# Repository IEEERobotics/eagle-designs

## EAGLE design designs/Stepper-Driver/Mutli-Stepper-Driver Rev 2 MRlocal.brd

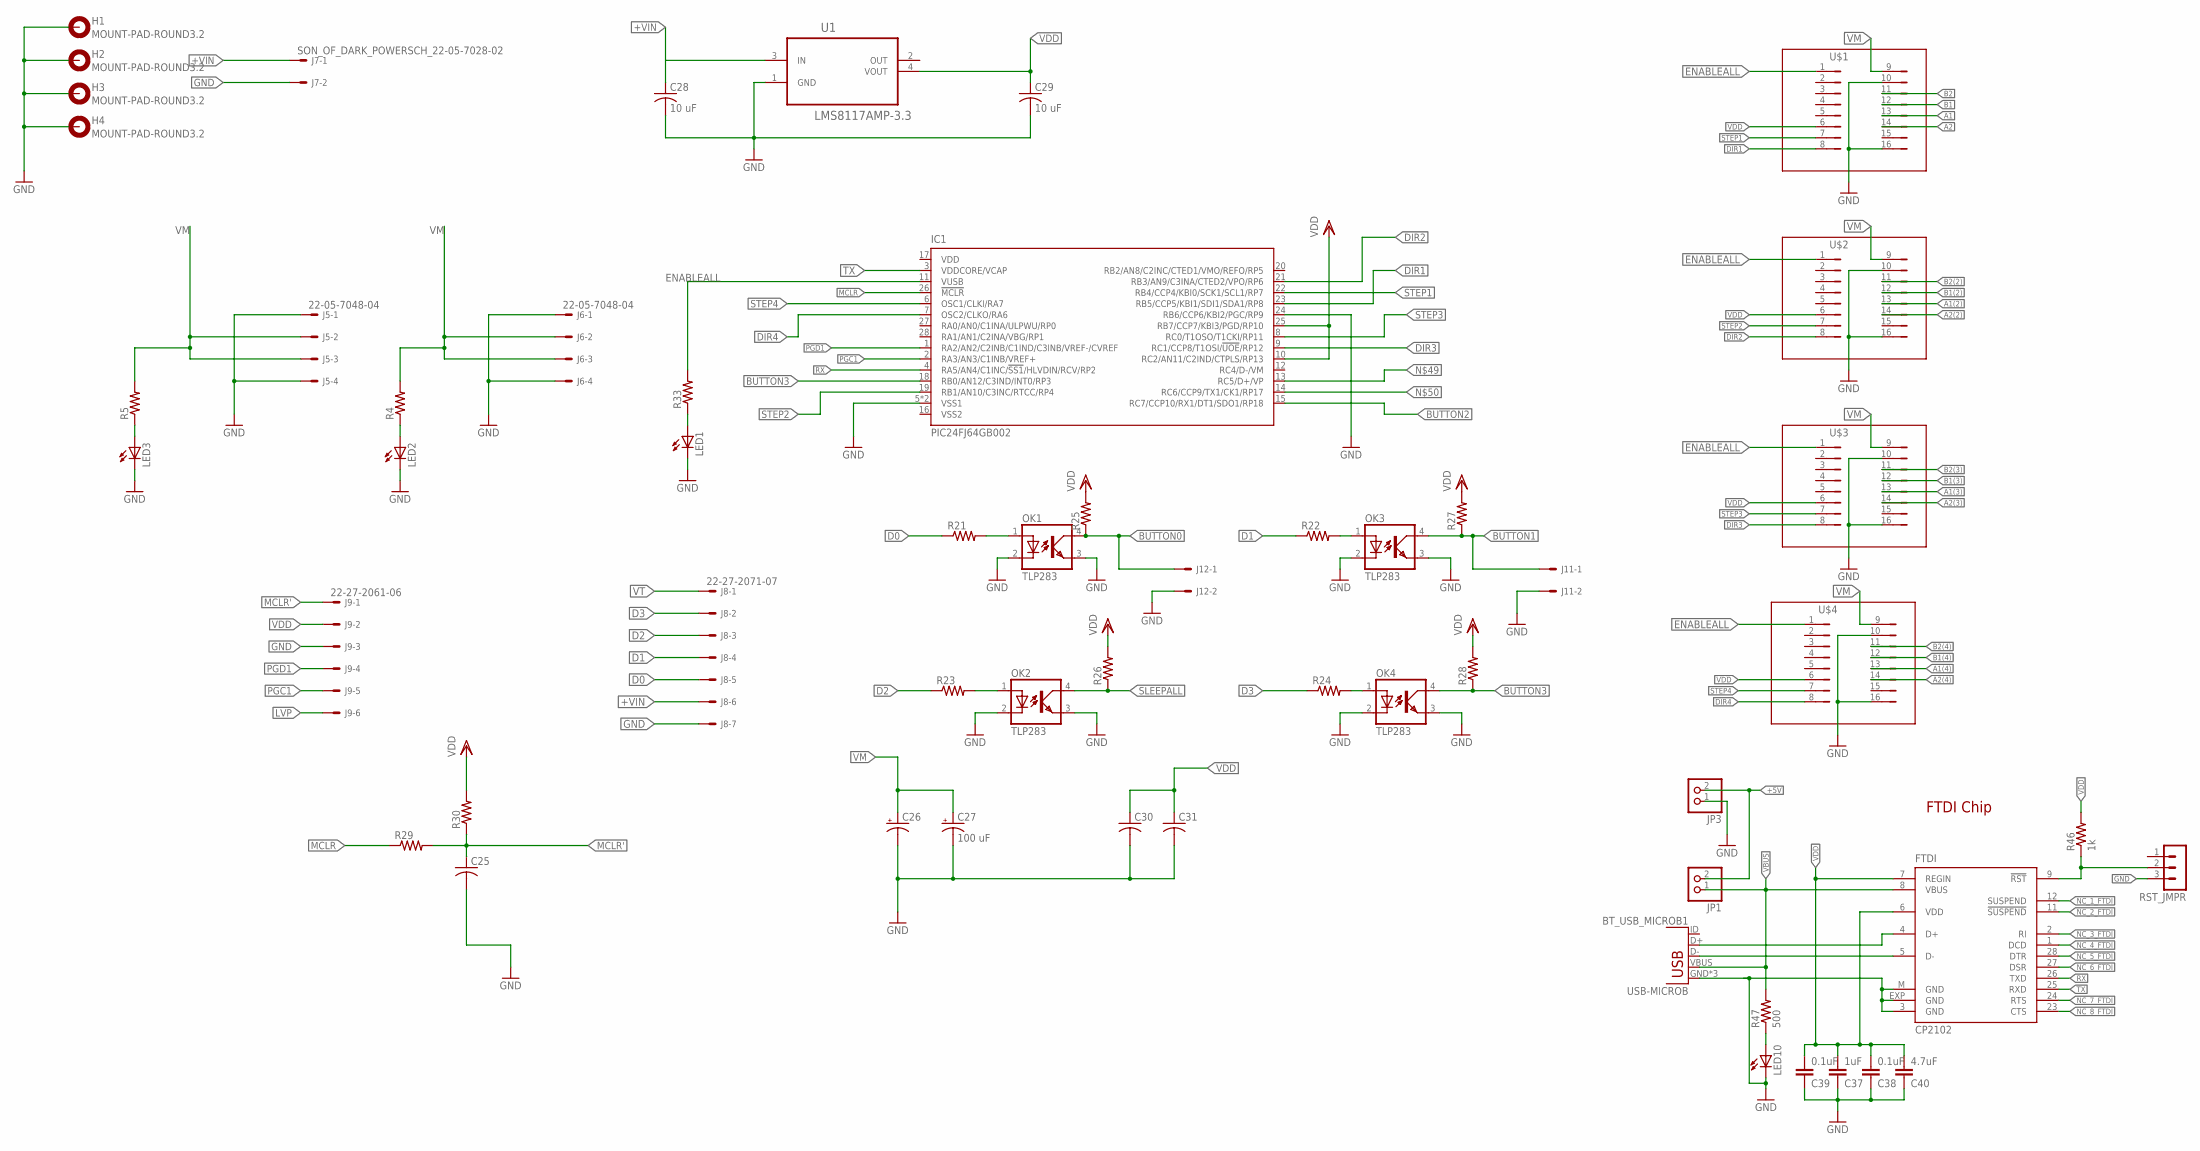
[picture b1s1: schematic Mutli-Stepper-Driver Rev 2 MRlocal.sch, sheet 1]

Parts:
BT_USB_MICROB1: USB-MICROB
C25, C30, C31: C-USC0805; C0805
C26: CPOL-USCT7343; CT7343
C27: 100 uF; CT7343
C28, C29: 10 uF; C3216
C37: 1uF; C0805
C38, C39: 0.1uF; C0805
C40: 4.7uF; C0805
FTDI: CP2102; MLP28
H1, H2, H3, H4: MOUNT-PAD-ROUND3.2; 3,2-PAD
IC1: PIC24FJ64GB002; MICROCHIP_QFN28-ML_6X6MM
J5, J6: 22-05-7048-04; 7395-04
J7, J11, J12: SON_OF_DARK_POWERSCH_22-05-7028-02; SON_OF_DARK_POWERSCH_7395-02
J8: 22-27-2071-07; 6410-07
J9: 22-27-2061-06; 6410-06
JP1, JP3: PINHD-1X2; 1X02
LED1, LED2, LED3: LEDCHIPLED_0805; CHIPLED_0805
LED10: LEDSML0603; SML0603
OK1, OK2, OK3, OK4: TLP283; MINI-FLAT-4
R4, R5, R21, R22, R23, R24, R25, R26, R27, R28, R29, R30, R33: R-US_R0805; R0805
R46: 1k; R0805
R47: 500; R0805
RST_JMPR: MA03-1
U1: LMS8117AMP-3.3; NSC-LMS8117AMP_SOT230P696X180-4N
U$1, U$2, U$3, U$4: DRIVER; 6410-08

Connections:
+5V: JP1.2, JP3.2
+VIN: C28.1, J7.1, J8.6, U1.3 (IN)
A1: U$1.13; also elsewhere on the board
A1(2): U$2.13; also elsewhere on the board
A1(3): U$3.13; also elsewhere on the board
A1(4): U$4.13; also elsewhere on the board
A2: U$1.14; also elsewhere on the board
A2(2): U$2.14; also elsewhere on the board
A2(3): U$3.14; also elsewhere on the board
A2(4): U$4.14; also elsewhere on the board
B1: U$1.12; also elsewhere on the board
B1(2): U$2.12; also elsewhere on the board
B1(3): U$3.12; also elsewhere on the board
B1(4): U$4.12; also elsewhere on the board
B2: U$1.11; also elsewhere on the board
B2(2): U$2.11; also elsewhere on the board
B2(3): U$3.11; also elsewhere on the board
B2(4): U$4.11; also elsewhere on the board
BT_D+: BT_USB_MICROB1.D+, FTDI.4 (D+)
BT_D-: BT_USB_MICROB1.D-, FTDI.5 (D-)
BUTTON0: J12.1, OK1.4 (COL), R25.1
BUTTON1: J11.1, OK3.4 (COL), R27.1
BUTTON2: IC1.15 (RC7/CCP10/RX1/DT1/SDO1/RP18)
BUTTON3: IC1.18 (RB0/AN12/C3IND/INT0/RP3), OK4.4 (COL), R28.1
D0: J8.5, R21.1
D1: J8.4, R22.1
D2: J8.3, R23.1
D3: J8.2, R24.1
DIR1: IC1.23 (RB5/CCP5/KBI1/SDI1/SDA1/RP8), U$1.8
DIR2: IC1.21 (RB3/AN9/C3INA/CTED2/VPO/RP6), U$2.8
DIR3: IC1.9 (RC1/CCP8/T1OSI/!UOE!/RP12), U$3.8
DIR4: IC1.7 (OSC2/CLKO/RA6), U$4.8
ENABLEALL: IC1.11 (VUSB), R33.2, U$1.1, U$2.1, U$3.1, U$4.1
GND: BT_USB_MICROB1.GND, BT_USB_MICROB1.MT1 (GND), BT_USB_MICROB1.MT2 (GND), C25.2, C26.-, C27.-, C28.2, C29.2, C30.2, C31.2, C37.1, C38.1, C39.1, C40.1, FTDI.3 (GND), FTDI.EXP (GND), FTDI.M (GND), H1.B3,2, H2.B3,2, H3.B3,2, H4.B3,2, IC1.5 (VSS1), IC1.24 (RB6/CCP6/KBI2/PGC/RP9), IC1.EXP (VSS1), J5.1, J5.4, J6.1, J6.4, J7.2, J8.7, J9.3, J11.2, J12.2, JP3.1, LED1.C, LED2.C, LED3.C, LED10.C, OK1.2 (C), OK1.3 (EMIT), OK2.2 (C), OK2.3 (EMIT), OK3.2 (C), OK3.3 (EMIT), OK4.2 (C), OK4.3 (EMIT), RST_JMPR.3, U1.1 (GND), U$1.10, U$1.16, U$2.10, U$2.16, U$3.10, U$3.16, U$4.10, U$4.16
LVP: J9.6
MCLR: IC1.26 (!MCLR), R29.1
MCLR': C25.1, J9.1, R29.2, R30.1
unnamed: LED2.A, R4.1
unnamed: FTDI.9 (!RST), R46.1, RST_JMPR.2
unnamed: LED10.A, R47.1
unnamed: LED3.A, R5.1
unnamed: OK2.1 (A), R23.2
unnamed: OK4.1 (A), R24.2
unnamed: LED1.A, R33.1
unnamed: OK1.1 (A), R21.2
unnamed: OK3.1 (A), R22.2
NC_1_FTDI: FTDI.12 (SUSPEND)
NC_2_FTDI: FTDI.11 (!SUSPEND)
NC_3_FTDI: FTDI.2 (RI)
NC_4_FTDI: FTDI.1 (DCD)
NC_5_FTDI: FTDI.28 (DTR)
NC_6_FTDI: FTDI.27 (DSR)
NC_7_FTDI: FTDI.24 (RTS)
NC_8_FTDI: FTDI.23 (CTS)
PGC1: IC1.2 (RA3/AN3/C1INB/VREF+), J9.5
PGD1: IC1.1 (RA2/AN2/C2INB/C1IND/C3INB/VREF-/CVREF), J9.4
RX: FTDI.26 (TXD), IC1.4 (RA5/AN4/C1INC/!SS1!/HLVDIN/RCV/RP2)
SLEEPALL: OK2.4 (COL), R26.1
STEP1: IC1.22 (RB4/CCP4/KBI0/SCK1/SCL1/RP7), U$1.7
STEP2: IC1.19 (RB1/AN10/C3INC/RTCC/RP4), U$2.7
STEP3: IC1.8 (RC0/T1OSO/T1CKI/RP11), U$3.7
STEP4: IC1.6 (OSC1/CLKI/RA7), U$4.7
TX: FTDI.25 (RXD), IC1.3 (VDDCORE/VCAP)
VBUS: BT_USB_MICROB1.VBUS, FTDI.8 (VBUS), JP1.1, R47.2
VDD: C29.1, C30.1, C31.1, C37.2, C38.2, C39.2, C40.2, FTDI.6 (VDD), FTDI.7 (REGIN), IC1.10 (RC2/AN11/C2IND/CTPLS/RP13), IC1.25 (RB7/CCP7/KBI3/PGD/RP10), J9.2, R25.2, R26.2, R27.2, R28.2, R30.2, R46.2, U1.4 (VOUT), U$1.6, U$2.6, U$3.6, U$4.6
VM: C26.+, C27.+, J5.2, J5.3, J6.2, J6.3, R4.2, R5.2, U$1.9, U$2.9, U$3.9, U$4.9
VT: J8.1

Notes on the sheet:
FTDI Chip

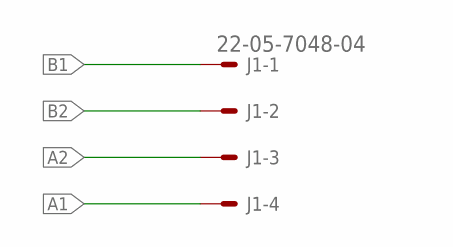
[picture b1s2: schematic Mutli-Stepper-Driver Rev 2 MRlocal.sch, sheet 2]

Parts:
J1: 22-05-7048-04; 7395-04

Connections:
A1: J1.4; also elsewhere on the board
A2: J1.3; also elsewhere on the board
B1: J1.1; also elsewhere on the board
B2: J1.2; also elsewhere on the board

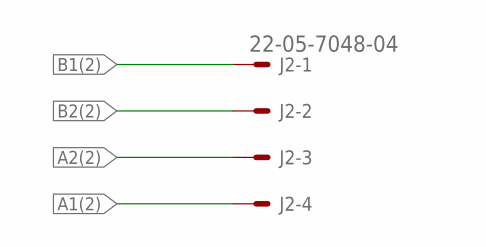
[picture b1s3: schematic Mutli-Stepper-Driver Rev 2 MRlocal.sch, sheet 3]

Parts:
J2: 22-05-7048-04; 7395-04

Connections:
A1(2): J2.4; also elsewhere on the board
A2(2): J2.3; also elsewhere on the board
B1(2): J2.1; also elsewhere on the board
B2(2): J2.2; also elsewhere on the board

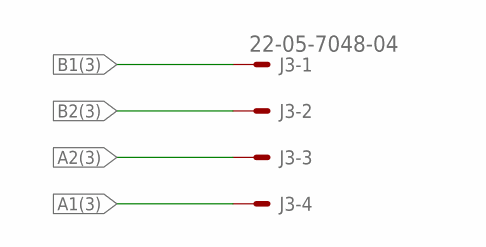
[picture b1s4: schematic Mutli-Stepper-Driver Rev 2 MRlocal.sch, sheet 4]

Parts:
J3: 22-05-7048-04; 7395-04

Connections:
A1(3): J3.4; also elsewhere on the board
A2(3): J3.3; also elsewhere on the board
B1(3): J3.1; also elsewhere on the board
B2(3): J3.2; also elsewhere on the board

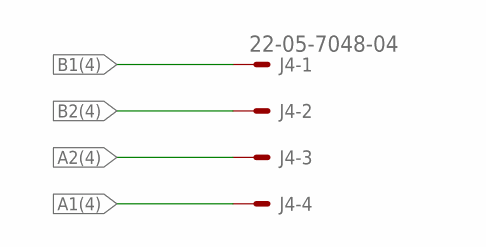
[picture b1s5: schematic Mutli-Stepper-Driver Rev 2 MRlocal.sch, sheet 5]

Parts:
J4: 22-05-7048-04; 7395-04

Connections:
A1(4): J4.4; also elsewhere on the board
A2(4): J4.3; also elsewhere on the board
B1(4): J4.1; also elsewhere on the board
B2(4): J4.2; also elsewhere on the board

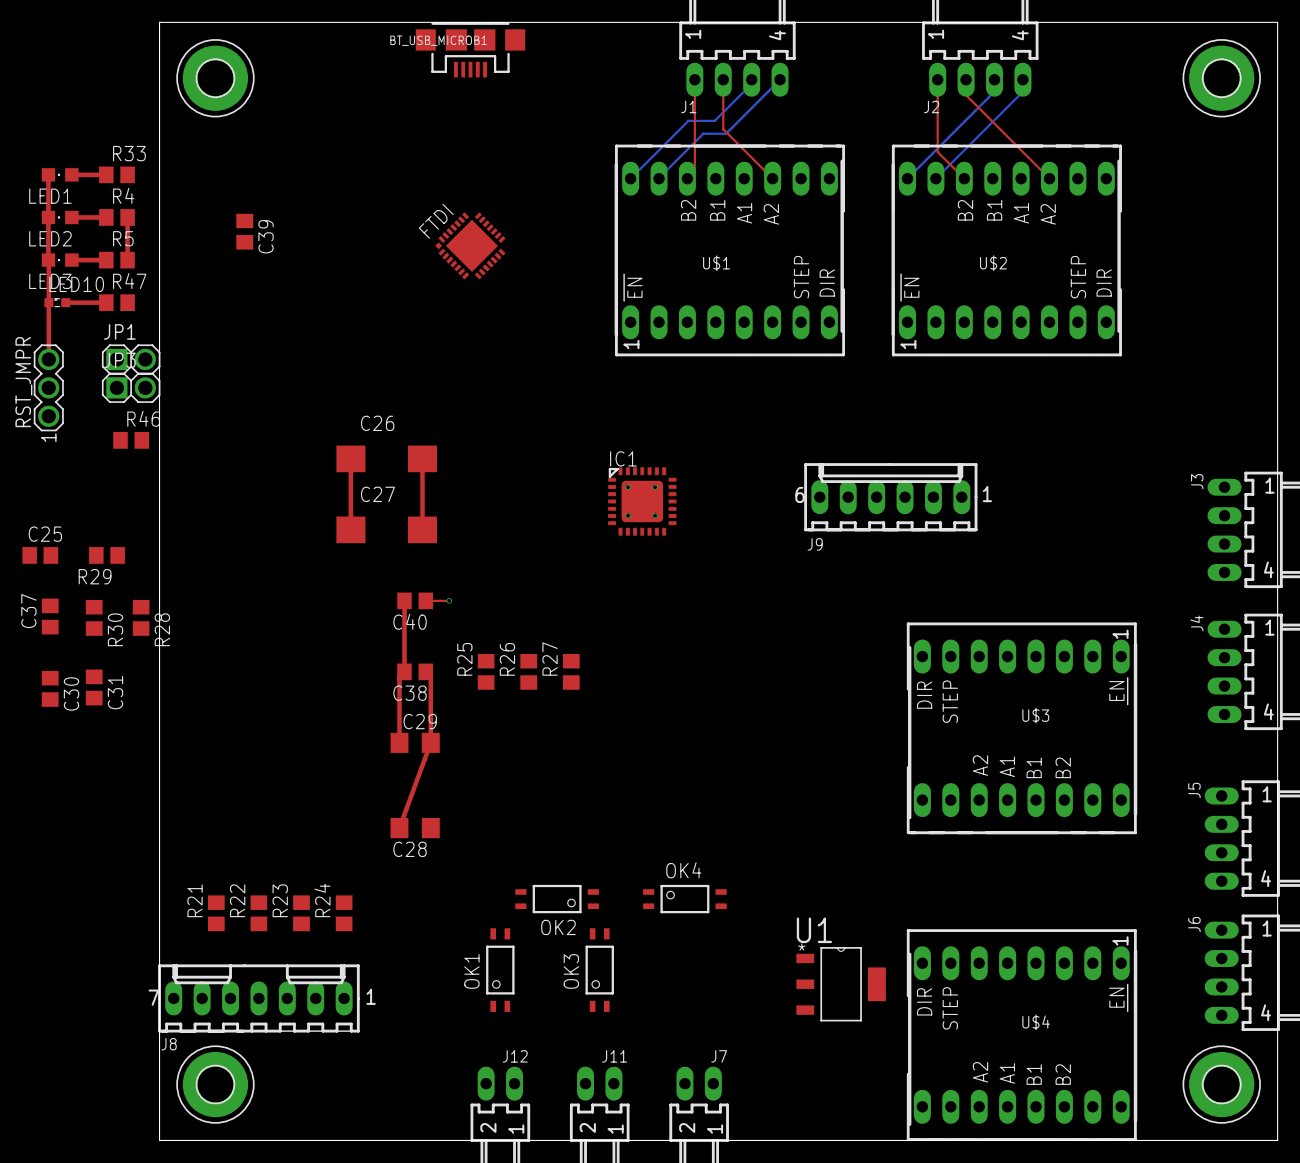
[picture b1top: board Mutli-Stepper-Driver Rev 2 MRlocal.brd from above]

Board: 2 copper layers, 100.0 x 100.0 mm, 60 parts (0 on the bottom side), 56 nets.

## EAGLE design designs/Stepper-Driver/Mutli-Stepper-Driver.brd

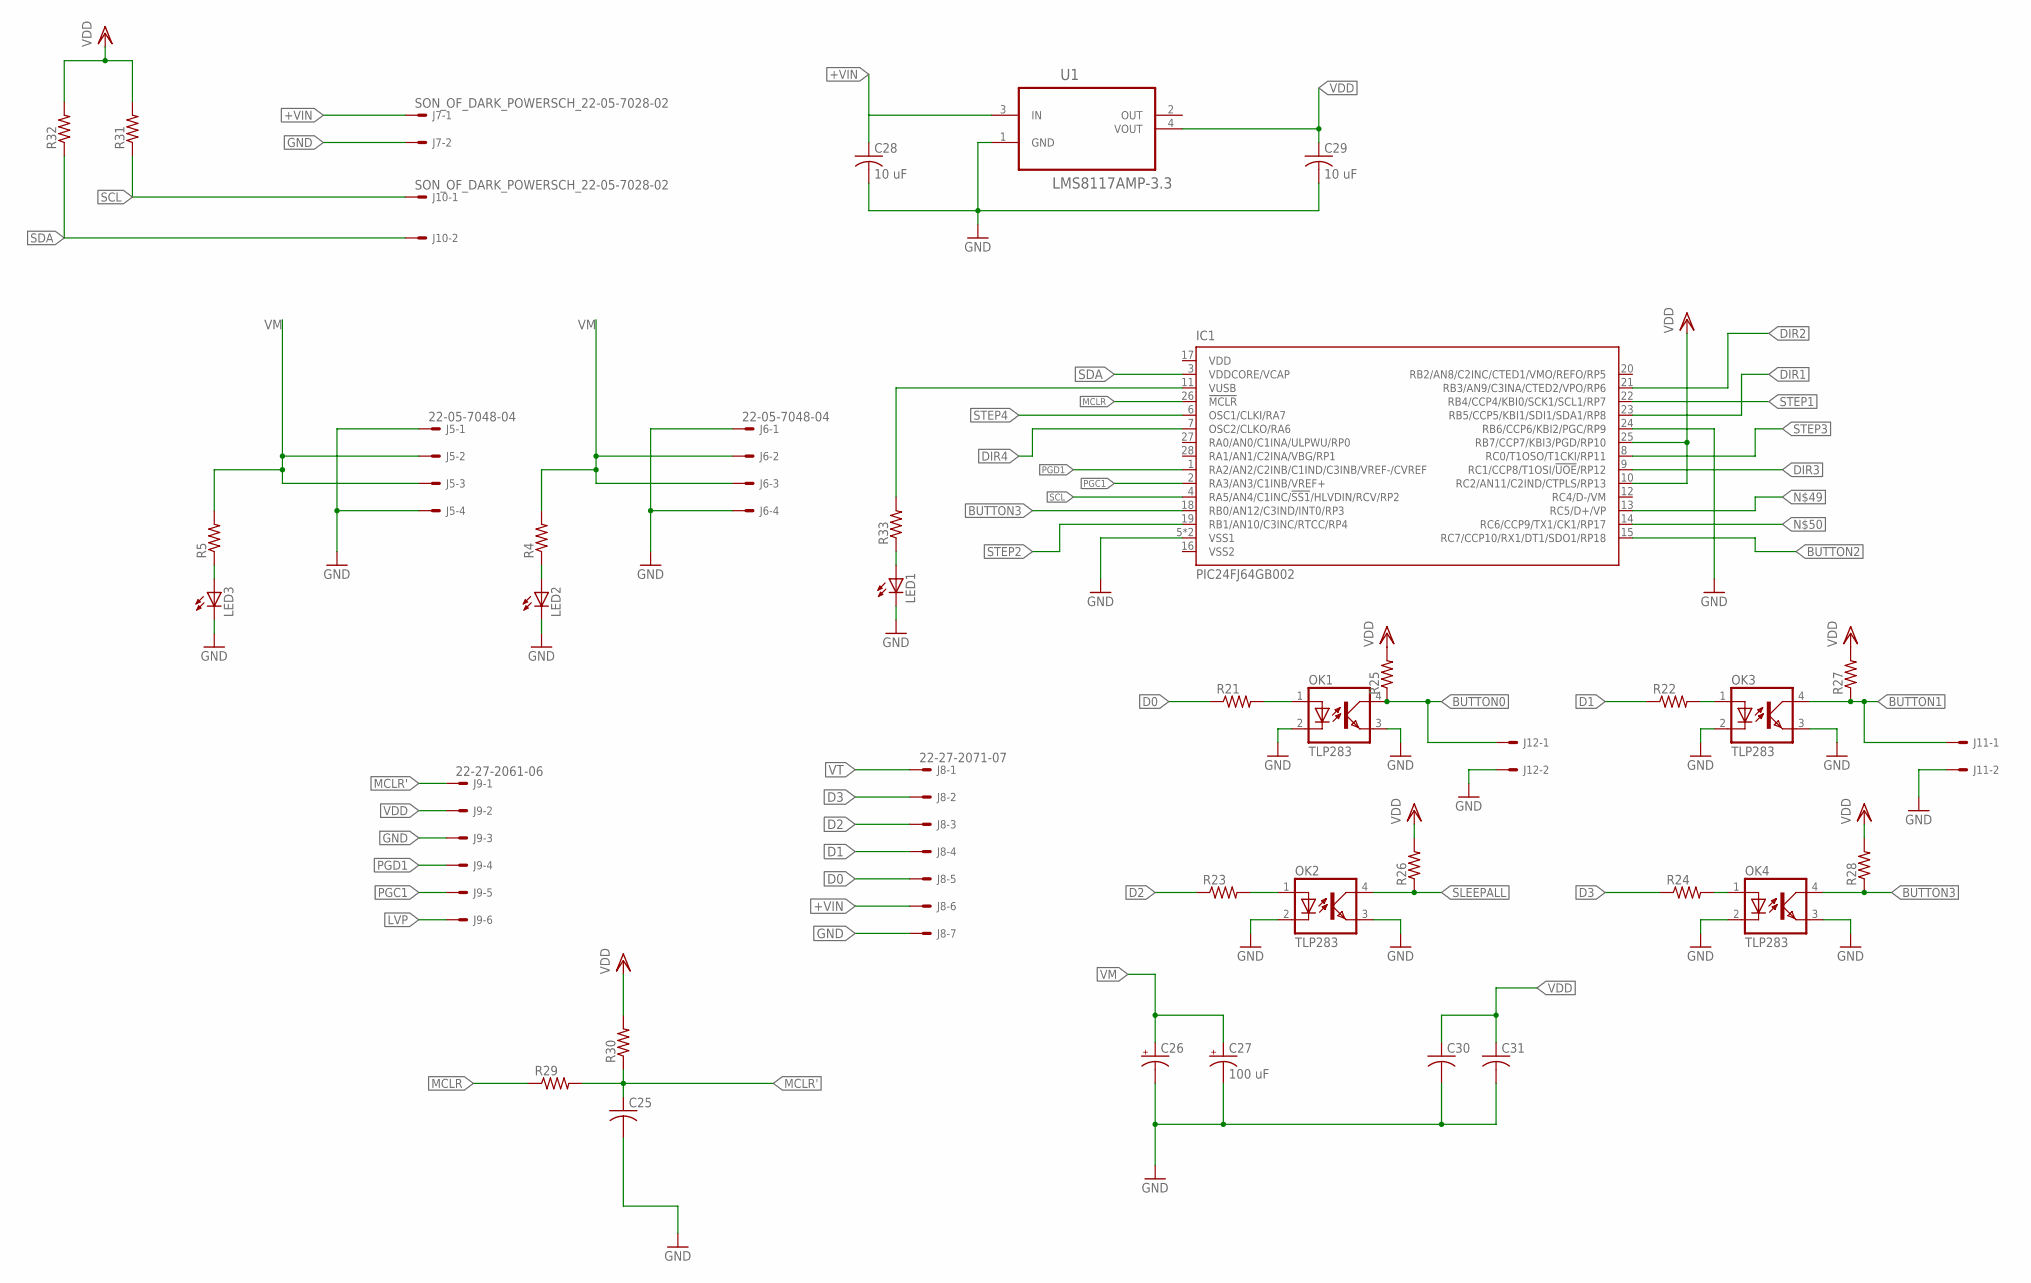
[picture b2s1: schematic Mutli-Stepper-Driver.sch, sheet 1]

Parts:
C25, C30, C31: C-USC0805; C0805
C26: CPOL-USCT7343; CT7343
C27: 100 uF; CT7343
C28, C29: 10 uF; C3216
IC1: PIC24FJ64GB002; MICROCHIP_QFN28-ML_6X6MM
J5, J6: 22-05-7048-04; 7395-04
J7, J10, J11, J12: SON_OF_DARK_POWERSCH_22-05-7028-02; SON_OF_DARK_POWERSCH_7395-02
J8: 22-27-2071-07; 6410-07
J9: 22-27-2061-06; 6410-06
LED1, LED2, LED3: LEDCHIPLED_0805; CHIPLED_0805
OK1, OK2, OK3, OK4: TLP283; MINI-FLAT-4
R4, R5, R21, R22, R23, R24, R25, R26, R27, R28, R29, R30, R31, R32, R33: R-US_R0805; R0805
U1: LMS8117AMP-3.3; NSC-LMS8117AMP_SOT230P696X180-4N

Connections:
+VIN: C28.1, J7.1, J8.6, U1.3 (IN)
BUTTON0: J12.1, OK1.4 (COL), R25.1
BUTTON1: J11.1, OK3.4 (COL), R27.1
BUTTON2: IC1.15 (RC7/CCP10/RX1/DT1/SDO1/RP18)
BUTTON3: IC1.18 (RB0/AN12/C3IND/INT0/RP3), OK4.4 (COL), R28.1
D0: J8.5, R21.1
D1: J8.4, R22.1
D2: J8.3, R23.1
D3: J8.2, R24.1
DIR1: IC1.23 (RB5/CCP5/KBI1/SDI1/SDA1/RP8); also elsewhere on the board
DIR2: IC1.21 (RB3/AN9/C3INA/CTED2/VPO/RP6); also elsewhere on the board
DIR3: IC1.9 (RC1/CCP8/T1OSI/!UOE!/RP12); also elsewhere on the board
DIR4: IC1.7 (OSC2/CLKO/RA6); also elsewhere on the board
GND: C25.2, C26.-, C27.-, C28.2, C29.2, C30.2, C31.2, IC1.5 (VSS1), IC1.24 (RB6/CCP6/KBI2/PGC/RP9), IC1.EXP (VSS1), J5.1, J5.4, J6.1, J6.4, J7.2, J8.7, J9.3, J11.2, J12.2, LED1.C, LED2.C, LED3.C, OK1.2 (C), OK1.3 (EMIT), OK2.2 (C), OK2.3 (EMIT), OK3.2 (C), OK3.3 (EMIT), OK4.2 (C), OK4.3 (EMIT), U1.1 (GND); also elsewhere on the board
LVP: J9.6
MCLR: IC1.26 (!MCLR), R29.1
MCLR': C25.1, J9.1, R29.2, R30.1
unnamed: LED2.A, R4.1
unnamed: LED3.A, R5.1
unnamed: OK2.1 (A), R23.2
unnamed: OK4.1 (A), R24.2
unnamed: LED1.A, R33.1
unnamed: OK1.1 (A), R21.2
unnamed: OK3.1 (A), R22.2
unnamed: IC1.11 (VUSB), R33.2
PGC1: IC1.2 (RA3/AN3/C1INB/VREF+), J9.5
PGD1: IC1.1 (RA2/AN2/C2INB/C1IND/C3INB/VREF-/CVREF), J9.4
SCL: IC1.4 (RA5/AN4/C1INC/!SS1!/HLVDIN/RCV/RP2), J10.1, R31.1
SDA: IC1.3 (VDDCORE/VCAP), J10.2, R32.1
SLEEPALL: OK2.4 (COL), R26.1; also elsewhere on the board
STEP1: IC1.22 (RB4/CCP4/KBI0/SCK1/SCL1/RP7); also elsewhere on the board
STEP2: IC1.19 (RB1/AN10/C3INC/RTCC/RP4); also elsewhere on the board
STEP3: IC1.8 (RC0/T1OSO/T1CKI/RP11); also elsewhere on the board
STEP4: IC1.6 (OSC1/CLKI/RA7); also elsewhere on the board
VDD: C29.1, C30.1, C31.1, IC1.10 (RC2/AN11/C2IND/CTPLS/RP13), IC1.25 (RB7/CCP7/KBI3/PGD/RP10), J9.2, R25.2, R26.2, R27.2, R28.2, R30.2, R31.2, R32.2, U1.4 (VOUT)
VM: C26.+, C27.+, J5.2, J5.3, J6.2, J6.3, R4.2, R5.2; also elsewhere on the board
VT: J8.1

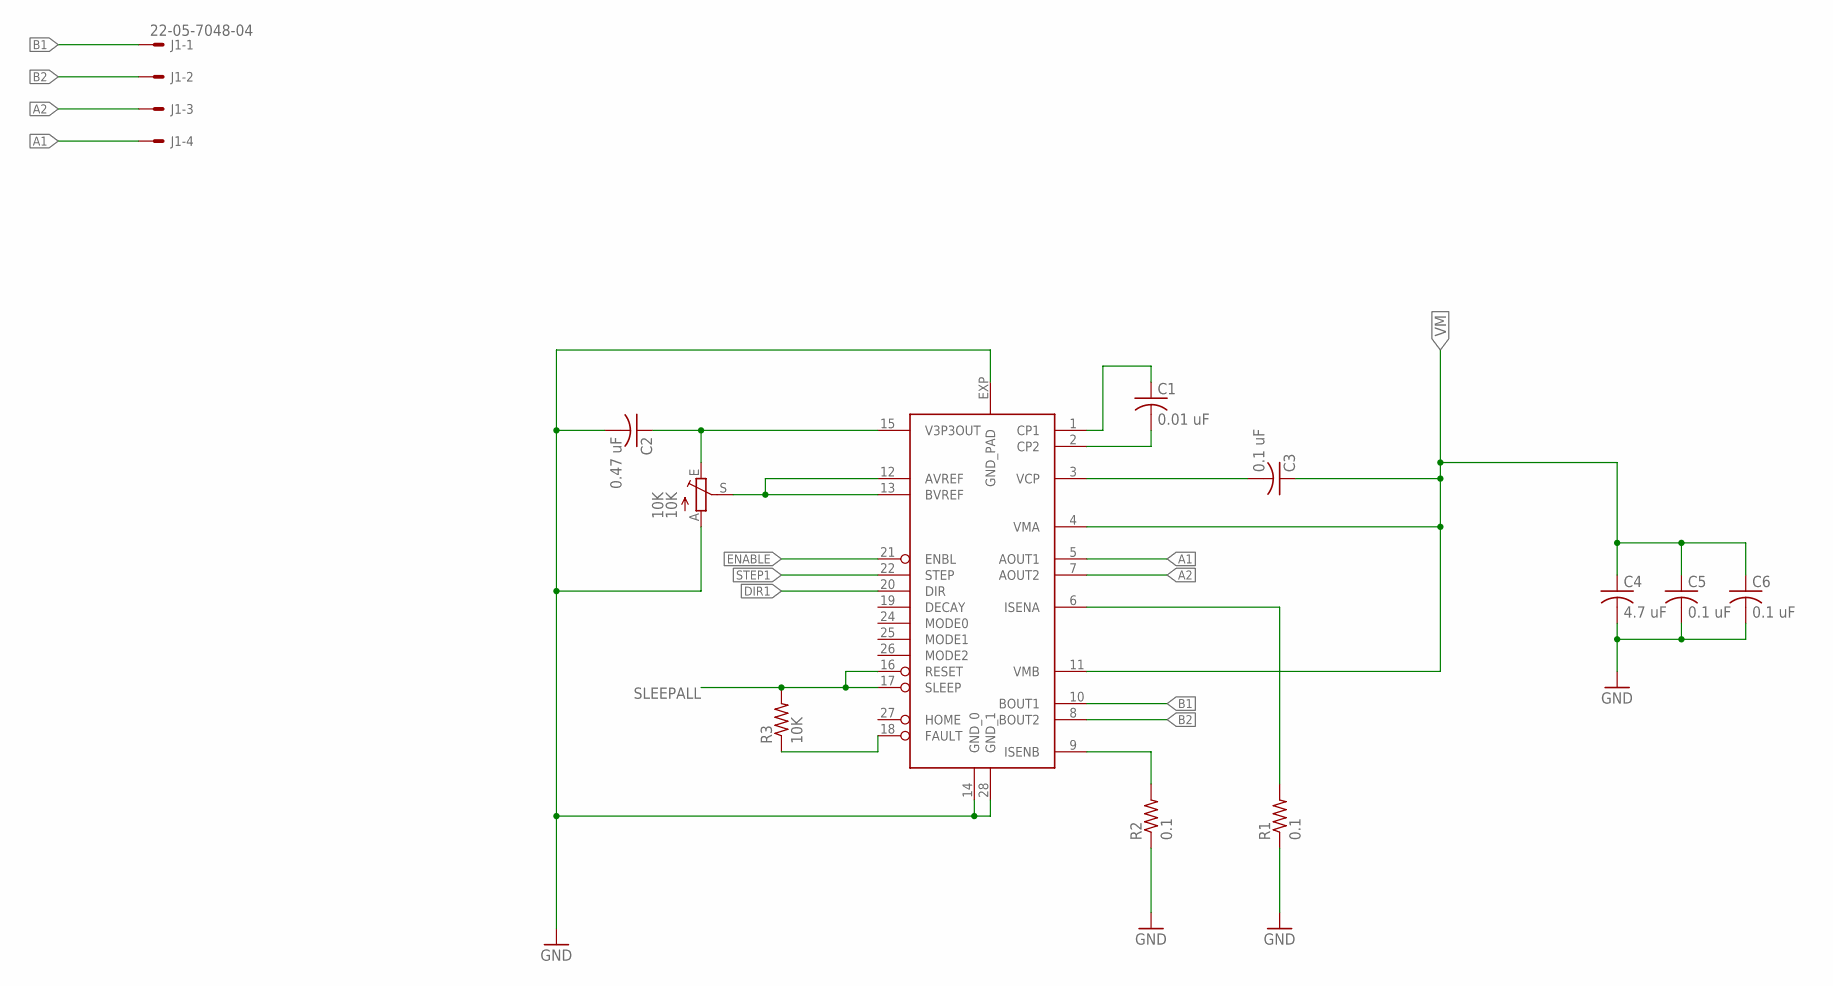
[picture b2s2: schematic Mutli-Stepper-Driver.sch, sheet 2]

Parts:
10K: 10K; CT6
C1: 0.01 uF; C0805
C2: 0.47 uF; C0805
C3, C5, C6: 0.1 uF; C0805
C4: 4.7 uF; C0805
J1: 22-05-7048-04; 7395-04
R1, R2: 0.1; R1206
R3: 10K; R0805
U$1: DRV8825PWP; TSSOP-28

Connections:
A1: J1.4, U$1.5 (AOUT1)
A2: J1.3, U$1.7 (AOUT2)
B1: J1.1, U$1.10 (BOUT1)
B2: J1.2, U$1.8 (BOUT2)
DIR1: U$1.20 (DIR); also elsewhere on the board
ENABLE: U$1.21 (ENBL); also elsewhere on the board
FAULT1: R3.1, U$1.18 (FAULT)
GND: 10K.A, C2.2, C4.2, C5.2, C6.2, R1.1, R2.1, U$1.14 (GND_0), U$1.28 (GND_1), U$1.EXP (GND_PAD); also elsewhere on the board
unnamed: C3.2, U$1.3 (VCP)
unnamed: R1.2, U$1.6 (ISENA)
unnamed: R2.2, U$1.9 (ISENB)
unnamed: 10K.S, U$1.12 (AVREF), U$1.13 (BVREF)
unnamed: 10K.E, C2.1, U$1.15 (V3P3OUT)
unnamed: C1.1, U$1.1 (CP1)
unnamed: C1.2, U$1.2 (CP2)
SLEEPALL: R3.2, U$1.16 (RESET), U$1.17 (SLEEP); also elsewhere on the board
STEP1: U$1.22 (STEP); also elsewhere on the board
VM: C3.1, C4.1, C5.1, C6.1, U$1.4 (VMA), U$1.11 (VMB); also elsewhere on the board

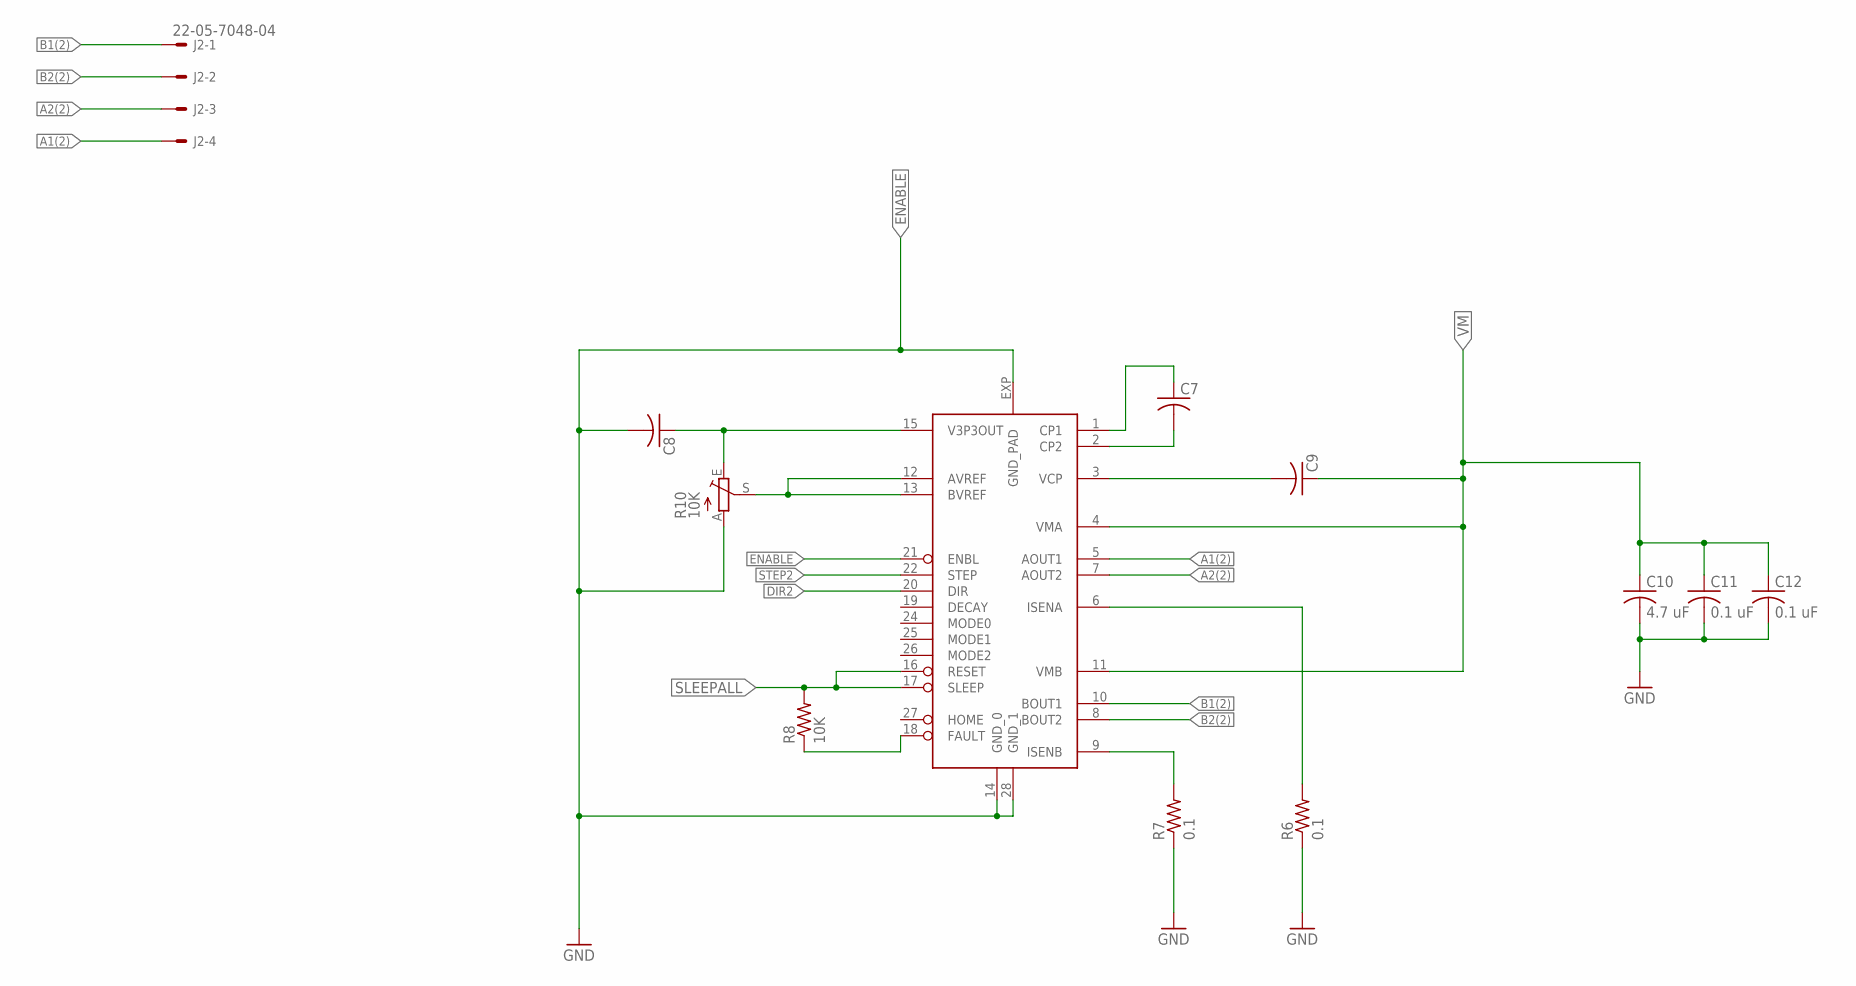
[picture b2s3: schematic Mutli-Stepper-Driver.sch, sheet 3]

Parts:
C7, C8, C9: C-USC0805; C0805
C10: 4.7 uF; C0805
C11, C12: 0.1 uF; C0805
J2: 22-05-7048-04; 7395-04
R6, R7: 0.1; R1206
R8: 10K; R0805
R10: 10K; CT6
U$2: DRV8825PWP; TSSOP-28

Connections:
A1(2): J2.4, U$2.5 (AOUT1)
A2(2): J2.3, U$2.7 (AOUT2)
B1(2): J2.1, U$2.10 (BOUT1)
B2(2): J2.2, U$2.8 (BOUT2)
DIR2: U$2.20 (DIR); also elsewhere on the board
ENABLE: C8.2, R10.A, U$2.14 (GND_0), U$2.21 (ENBL), U$2.28 (GND_1), U$2.EXP (GND_PAD); also elsewhere on the board
FAULT2: R8.1, U$2.18 (FAULT)
GND: C10.2, C11.2, C12.2, R6.1, R7.1; also elsewhere on the board
unnamed: R6.2, U$2.6 (ISENA)
unnamed: R7.2, U$2.9 (ISENB)
unnamed: C8.1, R10.E, U$2.15 (V3P3OUT)
unnamed: C7.1, U$2.1 (CP1)
unnamed: C7.2, U$2.2 (CP2)
unnamed: C9.2, U$2.3 (VCP)
unnamed: R10.S, U$2.12 (AVREF), U$2.13 (BVREF)
SLEEPALL: R8.2, U$2.16 (RESET), U$2.17 (SLEEP); also elsewhere on the board
STEP2: U$2.22 (STEP); also elsewhere on the board
VM: C9.1, C10.1, C11.1, C12.1, U$2.4 (VMA), U$2.11 (VMB); also elsewhere on the board

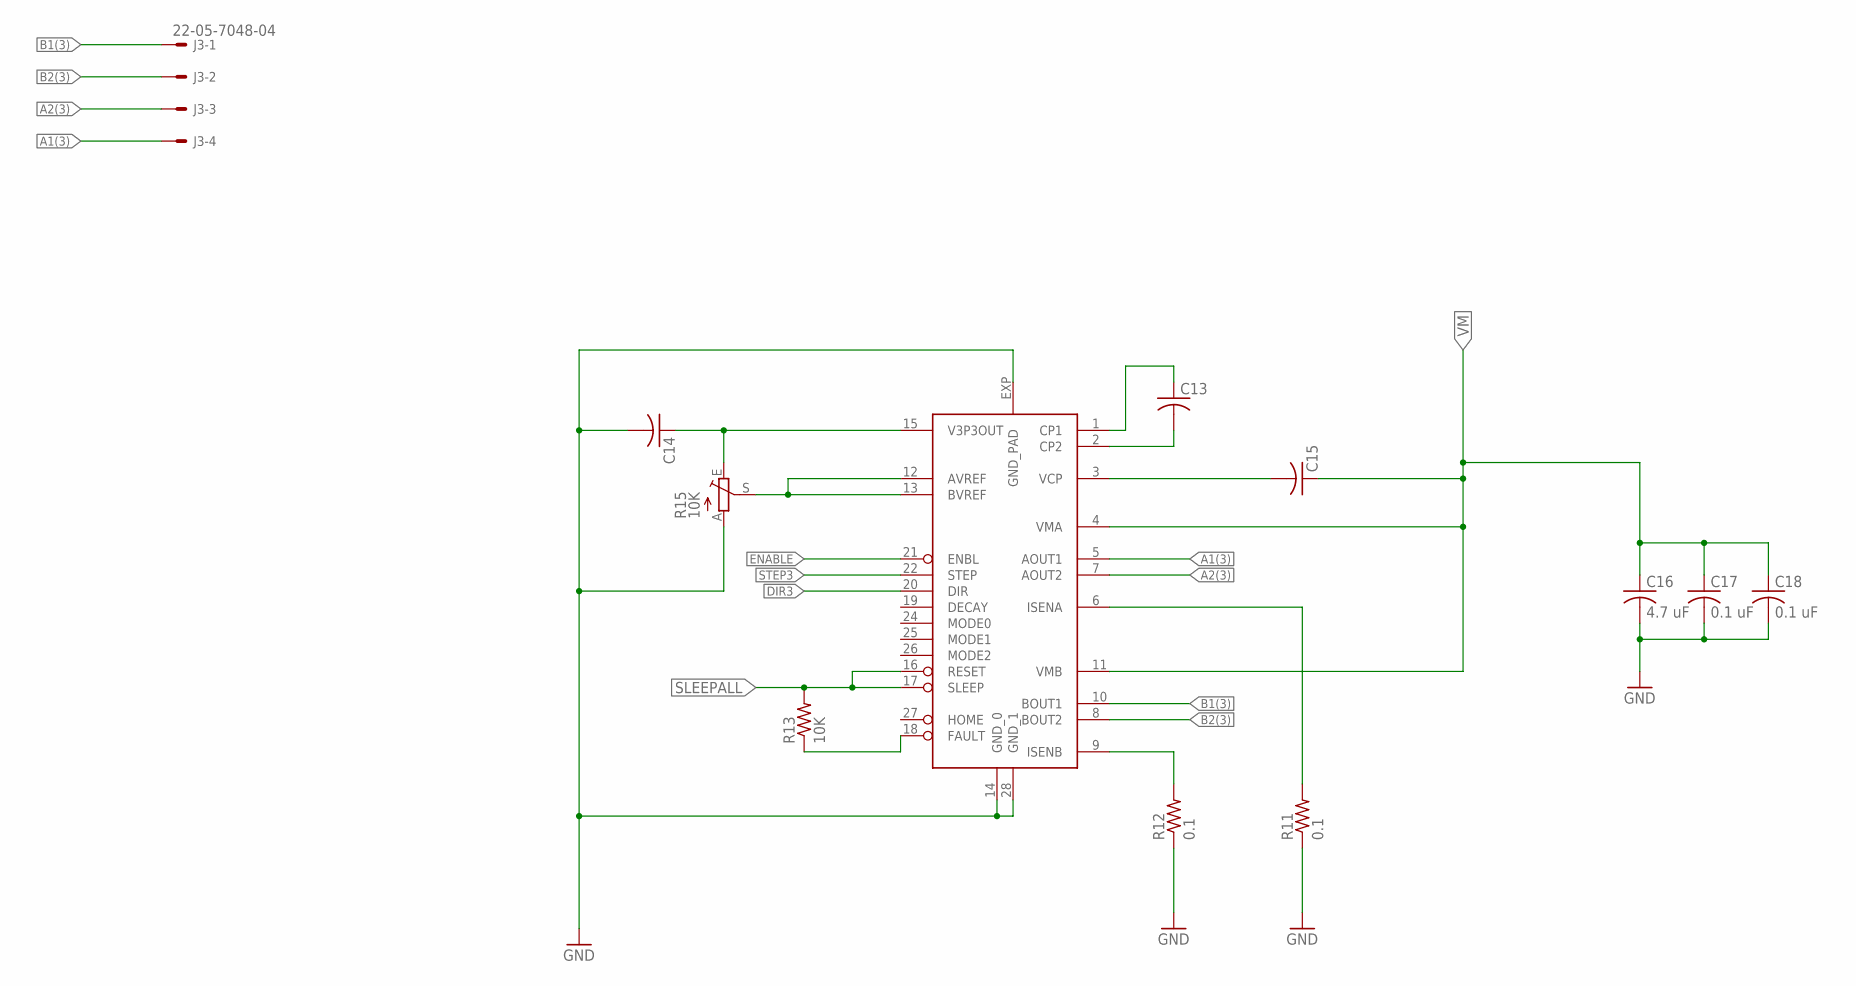
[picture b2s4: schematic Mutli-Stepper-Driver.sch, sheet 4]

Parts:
C13, C14, C15: C-USC0805; C0805
C16: 4.7 uF; C0805
C17, C18: 0.1 uF; C0805
J3: 22-05-7048-04; 7395-04
R11, R12: 0.1; R1206
R13: 10K; R0805
R15: 10K; CT6
U$3: DRV8825PWP; TSSOP-28

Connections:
A1(3): J3.4, U$3.5 (AOUT1)
A2(3): J3.3, U$3.7 (AOUT2)
B1(3): J3.1, U$3.10 (BOUT1)
B2(3): J3.2, U$3.8 (BOUT2)
DIR3: U$3.20 (DIR); also elsewhere on the board
ENABLE: U$3.21 (ENBL); also elsewhere on the board
FAULT3: R13.1, U$3.18 (FAULT)
GND: C14.2, C16.2, C17.2, C18.2, R11.1, R12.1, R15.A, U$3.14 (GND_0), U$3.28 (GND_1), U$3.EXP (GND_PAD); also elsewhere on the board
unnamed: R11.2, U$3.6 (ISENA)
unnamed: R12.2, U$3.9 (ISENB)
unnamed: C14.1, R15.E, U$3.15 (V3P3OUT)
unnamed: C13.1, U$3.1 (CP1)
unnamed: C13.2, U$3.2 (CP2)
unnamed: C15.2, U$3.3 (VCP)
unnamed: R15.S, U$3.12 (AVREF), U$3.13 (BVREF)
SLEEPALL: R13.2, U$3.16 (RESET), U$3.17 (SLEEP); also elsewhere on the board
STEP3: U$3.22 (STEP); also elsewhere on the board
VM: C15.1, C16.1, C17.1, C18.1, U$3.4 (VMA), U$3.11 (VMB); also elsewhere on the board

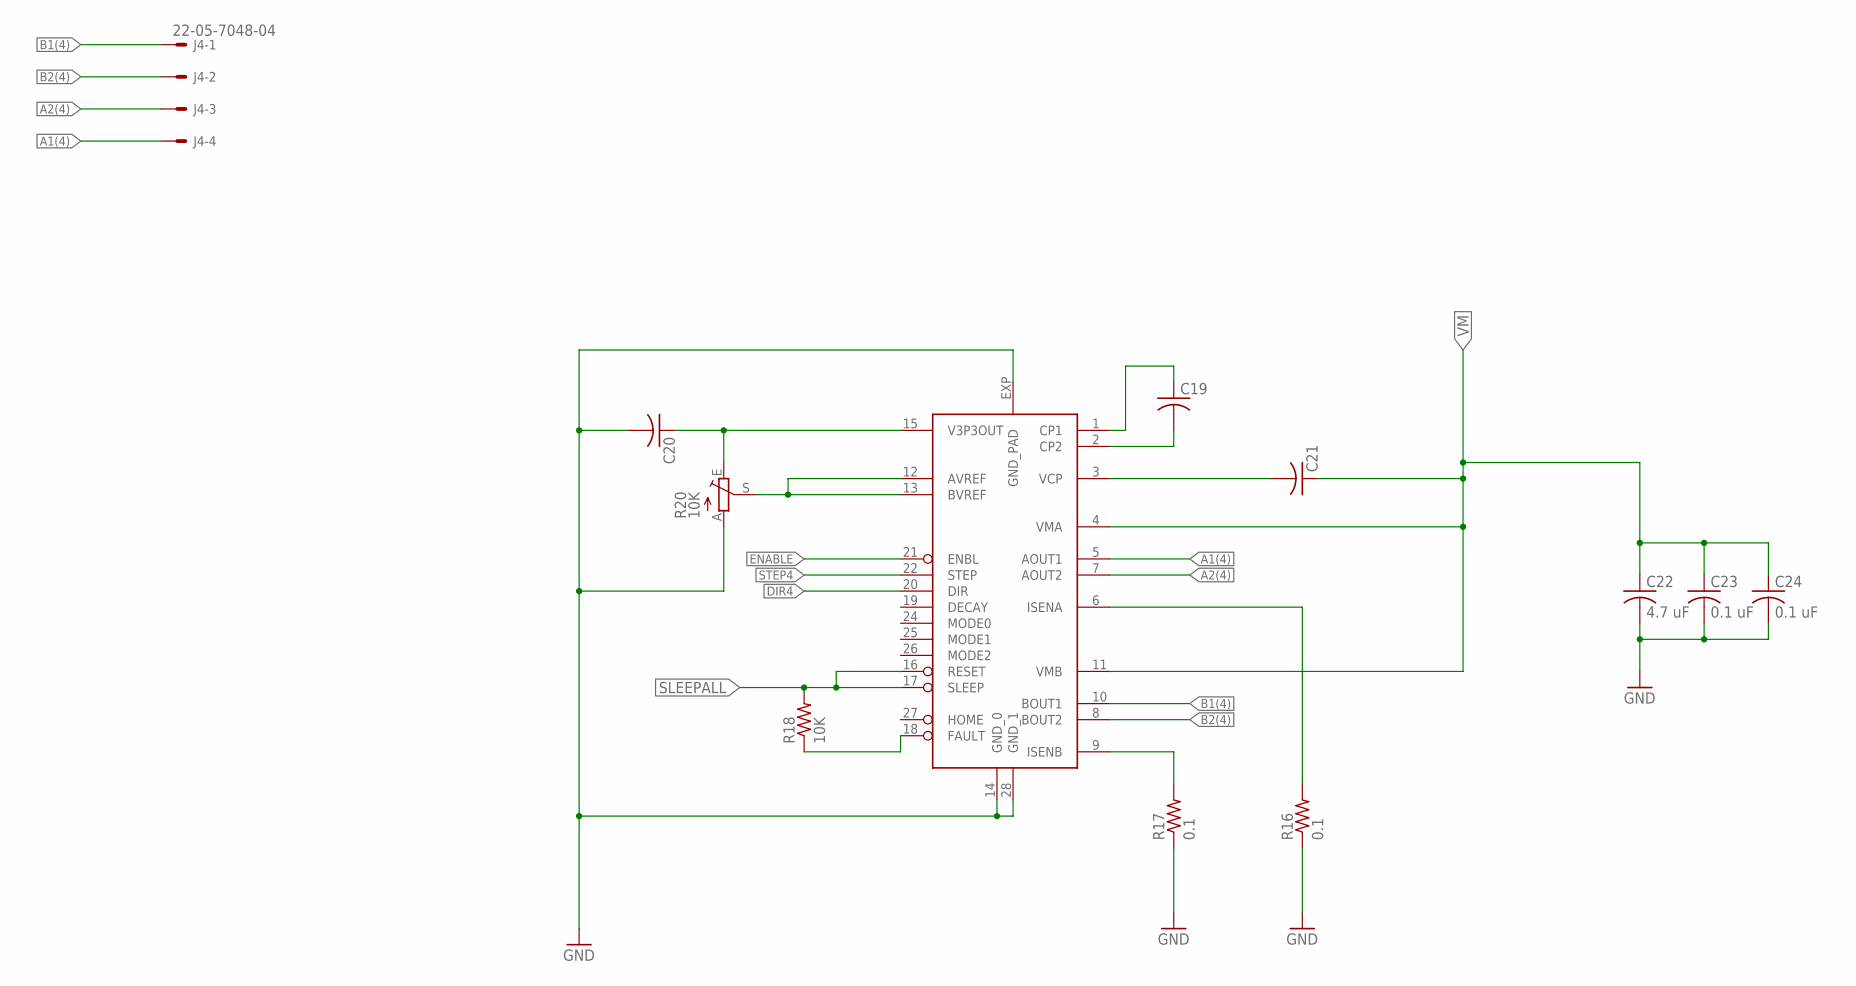
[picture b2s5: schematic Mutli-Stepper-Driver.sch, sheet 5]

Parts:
C19, C20, C21: C-USC0805; C0805
C22: 4.7 uF; C0805
C23, C24: 0.1 uF; C0805
J4: 22-05-7048-04; 7395-04
R16, R17: 0.1; R1206
R18: 10K; R0805
R20: 10K; CT6
U$4: DRV8825PWP; TSSOP-28

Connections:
A1(4): J4.4, U$4.5 (AOUT1)
A2(4): J4.3, U$4.7 (AOUT2)
B1(4): J4.1, U$4.10 (BOUT1)
B2(4): J4.2, U$4.8 (BOUT2)
DIR4: U$4.20 (DIR); also elsewhere on the board
ENABLE: U$4.21 (ENBL); also elsewhere on the board
FAULT4: R18.1, U$4.18 (FAULT)
GND: C20.2, C22.2, C23.2, C24.2, R16.1, R17.1, R20.A, U$4.14 (GND_0), U$4.28 (GND_1), U$4.EXP (GND_PAD); also elsewhere on the board
unnamed: R16.2, U$4.6 (ISENA)
unnamed: R17.2, U$4.9 (ISENB)
unnamed: C20.1, R20.E, U$4.15 (V3P3OUT)
unnamed: C19.1, U$4.1 (CP1)
unnamed: C19.2, U$4.2 (CP2)
unnamed: C21.2, U$4.3 (VCP)
unnamed: R20.S, U$4.12 (AVREF), U$4.13 (BVREF)
SLEEPALL: R18.2, U$4.16 (RESET), U$4.17 (SLEEP); also elsewhere on the board
STEP4: U$4.22 (STEP); also elsewhere on the board
VM: C21.1, C22.1, C23.1, C24.1, U$4.4 (VMA), U$4.11 (VMB); also elsewhere on the board

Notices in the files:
parts and their libraries:
SparkFun-Aesthetics: Licensing: Creative Commons ShareAlike 4.0 International - https://creativecommons.org/licenses/by-sa/4.0
